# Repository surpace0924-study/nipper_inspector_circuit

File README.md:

# nipper_inspector_circuit
回路図関係のものをまとめていきます

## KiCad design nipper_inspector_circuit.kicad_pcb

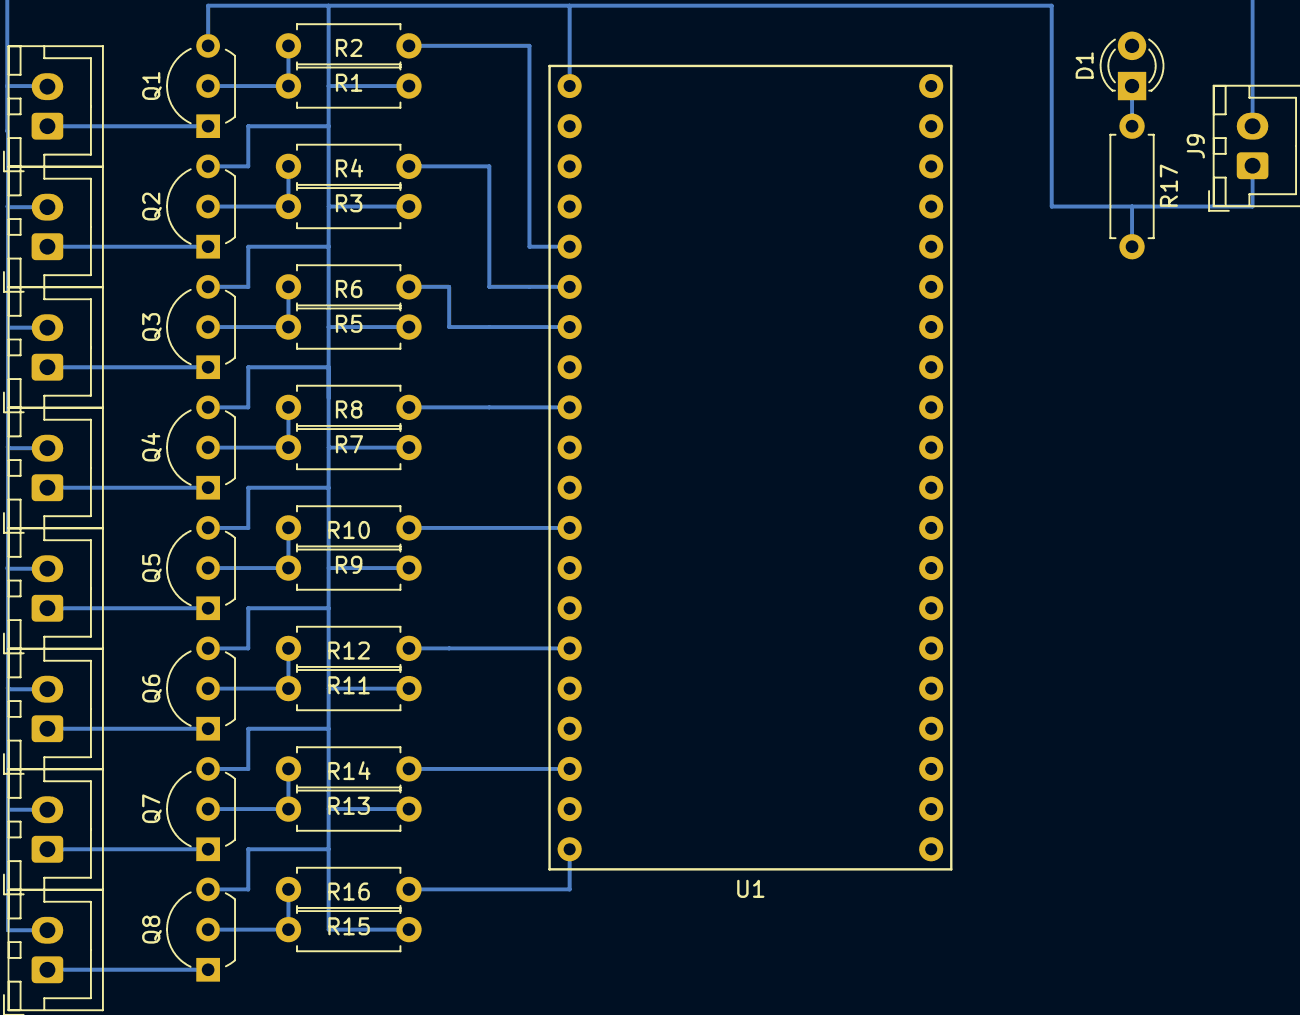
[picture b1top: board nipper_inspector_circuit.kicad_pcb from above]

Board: 2 copper layers, 36 parts (0 on the bottom side), 27 nets.

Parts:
D1: LED; LED_D3.0mm
J1, J2, J3, J4, J5, J6, J7, J8, J9: Conn_01x02_Male; JST_XH_B2B-XH-A_1x02_P2.50mm_Vertical
Q1, Q2, Q3, Q4, Q5, Q6, Q7, Q8: Q_NJFET_DGS; TO-92L_Inline_Wide
R1, R3, R5, R7, R9, R11, R13, R15: 100; R_Axial_DIN0207_L6.3mm_D2.5mm_P7.62mm_Horizontal
R2, R4, R6, R8, R10, R12, R14, R16, R17: 3.3k; R_Axial_DIN0207_L6.3mm_D2.5mm_P7.62mm_Horizontal
U1: LPC1768

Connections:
+12V: D1.2, J1.2, J2.2, J3.2, J4.2, J5.2, J6.2, J7.2, J8.2, J9.2
GND: J9.1, Q1.3, Q2.3, Q3.3, Q4.3, Q5.3, Q6.3, Q7.3, Q8.3, R2.2, R4.2, R6.2, R8.2, R10.2, R12.2, R14.2, R16.2, R17.2, U1.1
unnamed: D1.1, R17.1
unnamed: J1.1, Q1.1
unnamed: J2.1, Q2.1
unnamed: J3.1, Q3.1
unnamed: J4.1, Q4.1
unnamed: J5.1, Q5.1
unnamed: J6.1, Q6.1
unnamed: J7.1, Q7.1
unnamed: J8.1, Q8.1
unnamed: Q1.2, R1.2, R2.1
unnamed: Q2.2, R3.2, R4.1
unnamed: Q3.2, R5.2, R6.1
unnamed: Q4.2, R7.2, R8.1
unnamed: Q5.2, R9.2, R10.1
unnamed: Q6.2, R11.2, R12.1
unnamed: Q7.2, R13.2, R14.1
unnamed: Q8.2, R15.2, R16.1
sig0: R1.1, U1.5
sig1: R3.1, U1.6
sig2: R5.1, U1.7
sig3: R7.1, U1.9
sig4: R9.1, U1.12
sig5: R11.1, U1.15
sig6: R13.1, U1.18
sig7: R15.1, U1.20
